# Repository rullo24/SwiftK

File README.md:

# SwiftK
SwiftK is an open-source project for creating a customizable macro keypad that integrates seamlessly with your workflow. Designed for developers, gamers, and productivity enthusiasts, SwiftK provides a streamlined way to enhance your interaction with your computer through user-defined macros.

## About SwiftK
SwiftK was created to make repetitive tasks more efficient by providing a versatile macro keypad solution. With customizable keys, users can map complex command sequences or simple shortcuts, tailored to their needs. SwiftK aims to make interactions more productive and enjoyable for users in programming, gaming, content creation, and more.

This GitHub repo holds the KiCAD files required for the creation of this electronic board.

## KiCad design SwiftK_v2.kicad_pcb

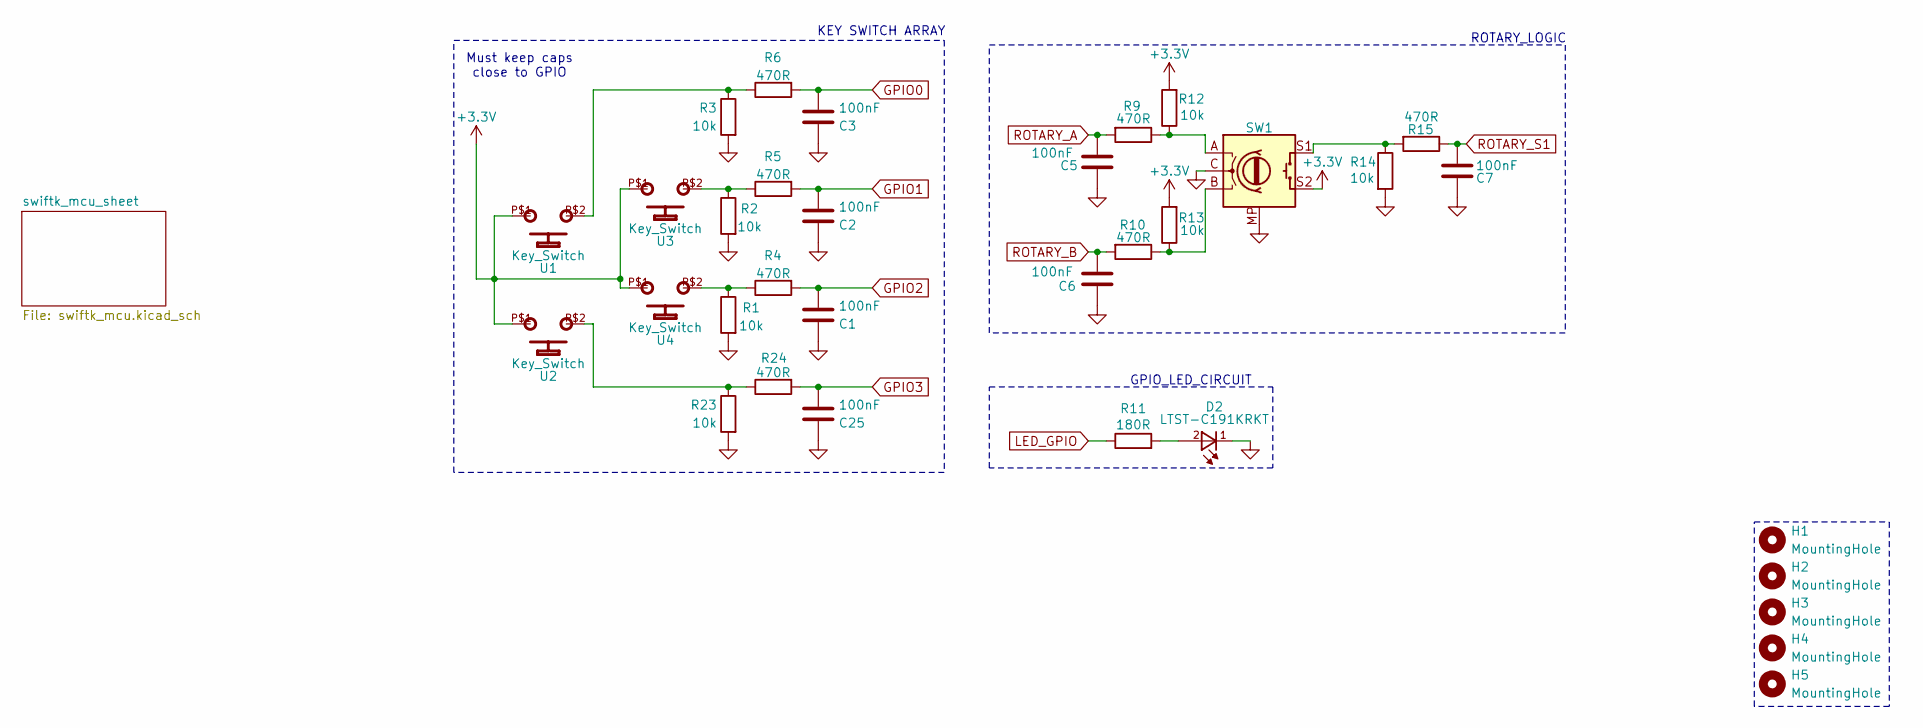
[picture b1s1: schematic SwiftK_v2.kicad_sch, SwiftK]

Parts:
C1, C2, C3, C5, C6, C7, C25: 100nF; C_0201_0603Metric; JLCPCB Part# C76928
D2: LTST-C191KRKT; liteon_LTST-C191KRKT; JLCPCB Part# C125099
H1, H2, H3, H4, H5: MountingHole; MountingHole_3.2mm_M3_DIN965_Pad
R1, R2, R3, R12, R13, R23: 10k; R_0201_0603Metric; JLCPCB Part# C100126
R4, R5, R6, R9, R10, R15, R24: 470R; R_0603_1608Metric; JLCPCB Part# C374403
R11: 180R; R_0603_1608Metric; JLCPCB Part# C25210
R14: 10k; R_0603_1608Metric; JLCPCB Part# C15401
SW1: RotaryEncoder_Switch_MP; RotaryEncoder_Alps_EC11E-Switch_Vertical_H20mm
U1, U2, U3, U4: Key_Switch; CHERRY_MX1A-11NN_SWITCH

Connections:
+3.3V: R12.2, R13.2, SW1.S2, U1.P$1, U2.P$1, U3.P$1, U4.P$1; also elsewhere on the board
GND: C1.1, C2.1, C3.1, C5.2, C6.2, C7.2, C25.1, D2.1, R1.2, R2.2, R3.2, R14.2, R23.2, SW1.C, SW1.MP; also elsewhere on the board
GPIO0: C3.2, R6.2; also elsewhere on the board
GPIO1: C2.2, R5.2; also elsewhere on the board
GPIO2: C1.2, R4.2; also elsewhere on the board
GPIO3: C25.2, R24.2; also elsewhere on the board
LED_GPIO: R11.1; also elsewhere on the board
unnamed: D2.2, R11.2
unnamed: R1.1, R4.1, U4.P$2
unnamed: R2.1, R5.1, U3.P$2
unnamed: R3.1, R6.1, U1.P$2
unnamed: R10.1, R13.1, SW1.B
unnamed: R9.1, R12.1, SW1.A
unnamed: R14.1, R15.2, SW1.S1
unnamed: R23.1, R24.1, U2.P$2
ROTARY_A: C5.1, R9.2; also elsewhere on the board
ROTARY_B: C6.1, R10.2; also elsewhere on the board
ROTARY_S1: C7.1, R15.1; also elsewhere on the board

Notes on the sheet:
Must keep caps close to GPIO
GPIO_LED_CIRCUIT
ROTARY_LOGIC
KEY SWITCH ARRAY

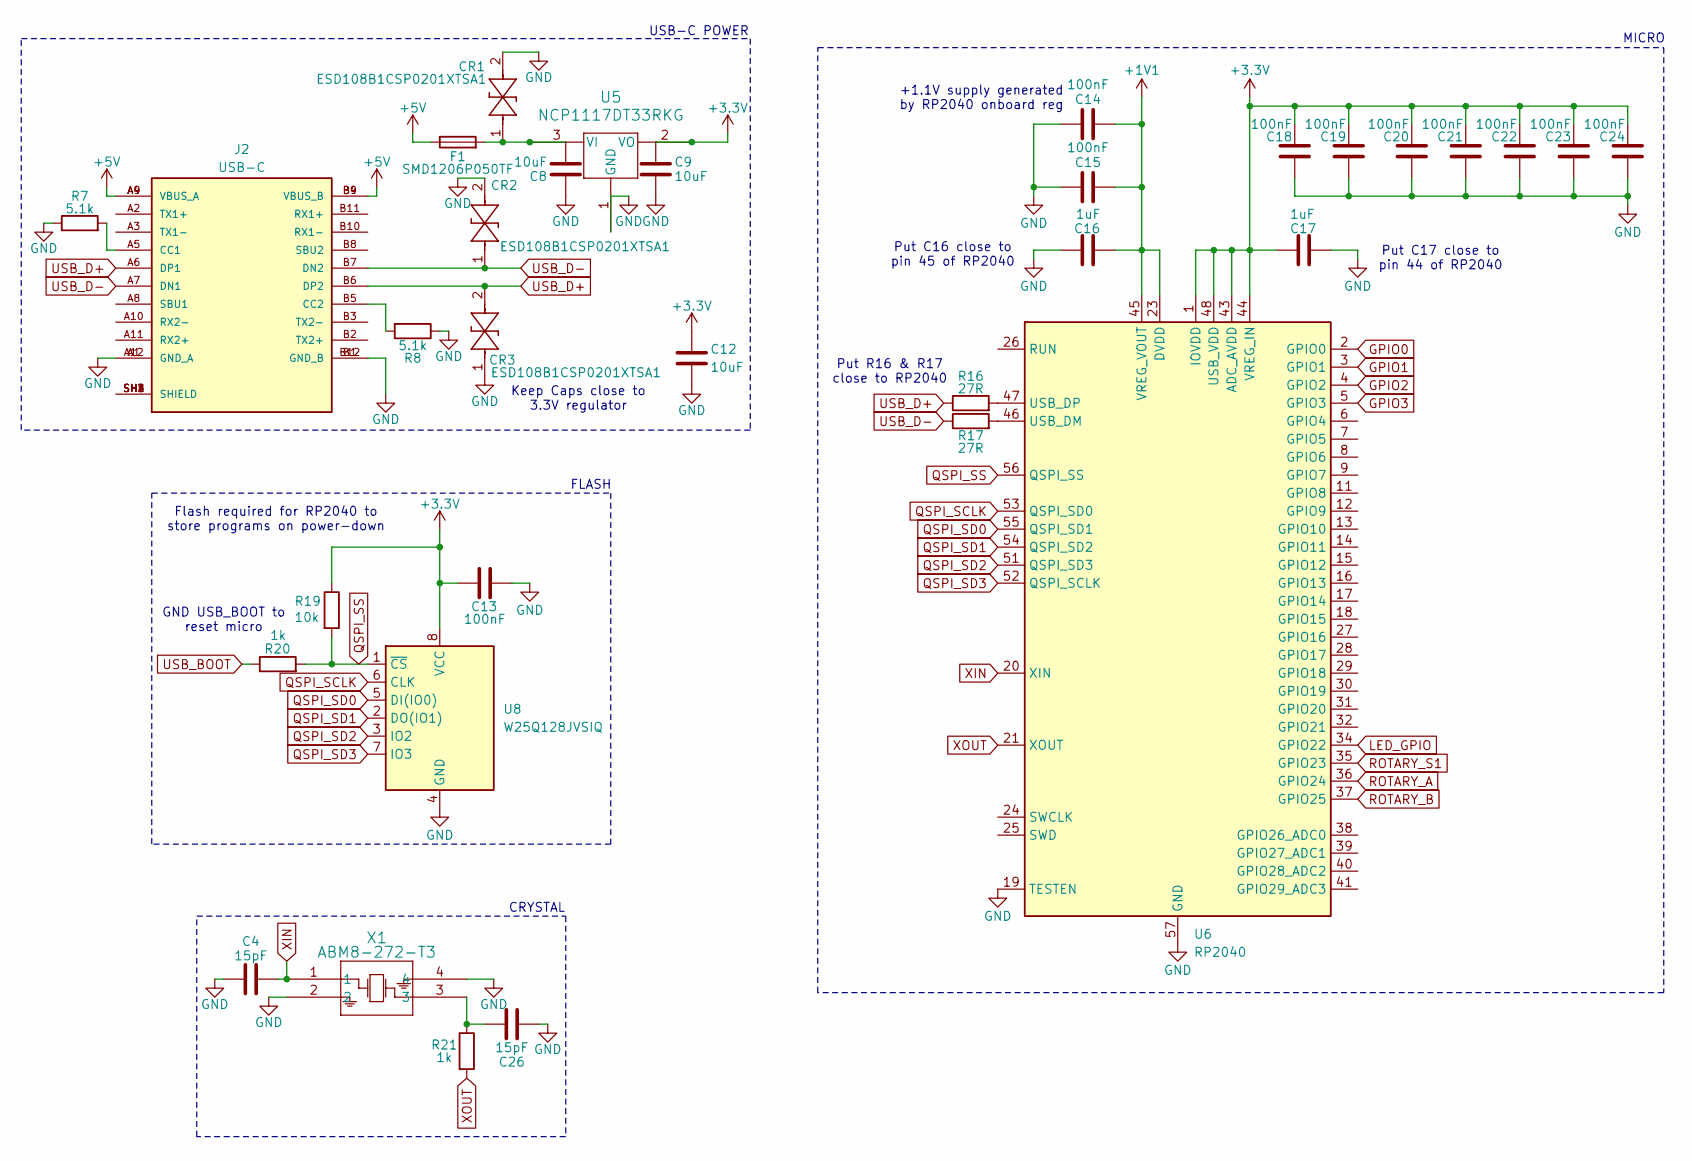
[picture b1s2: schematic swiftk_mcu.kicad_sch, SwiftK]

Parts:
C4, C26: 15pF; C_0603_1608Metric; JLCPCB Part# C1644
C8, C9, C12: 10uF; C_0603_1608Metric; JLCPCB Part# C18800
C13, C14, C15, C18, C19, C20, C21, C22, C23, C24: 100nF; C_0201_0603Metric; JLCPCB Part# C76928
C16, C17: 1uF; C_0201_0603Metric; JLCPCB Part# C76929
CR1, CR2, CR3: ESD108B1CSP0201XTSA1; Infineon_ESD108B1CSP0201XTSA1_L; JLCPCB Part# C672056
F1: SMD1206P050TF; Fuse_1206_3216Metric; JLCPCB Part# C20799
J2: USB-C; te_connectivity_2345986-1; JLCPCB Part# C5382687
R7, R8: 5.1k; R_0201_0603Metric; JLCPCB Part# C100142
R16, R17: 27R; R_1206_3216Metric; JLCPCB Part# C17946
R19: 10k; R_0603_1608Metric; JLCPCB Part# C15401
R20, R21: 1k; R_0603_1608Metric; JLCPCB Part# C51218
U5: NCP1117DT33RKG; onsemi_NCP1117DT33RKG_S; JLCPCB Part# C88234
U6: RP2040; QFN-56-1EP_7x7mm_P0.4mm_EP3.2x3.2mm; JLCPCB Part# C2040
U8: W25Q128JVSIQ; Winbond_Elec_W25Q128JVSIQ; JLCPCB Part# C97521
X1: ABM8-272-T3; Abracon_LLC_ABM8-272-T3; JLCPCB Part# C20625731

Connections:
+1V1: C14.2, C15.2, C16.1, U6.23 (DVDD), U6.45 (VREG_VOUT), U6.50 (DVDD)
+3.3V: C9.1, C12.1, C13.2, C17.2, C18.2, C19.2, C20.2, C21.2, C22.2, C23.2, C24.2, R19.1, U5.2 (VO), U6.1 (IOVDD), U6.10 (IOVDD), U6.22 (IOVDD), U6.33 (IOVDD), U6.42 (IOVDD), U6.43 (ADC_AVDD), U6.44 (VREG_IN), U6.48 (USB_VDD), U6.49 (IOVDD), U8.8 (VCC); also elsewhere on the board
+5V: F1.1, J2.A4 (VBUS_A), J2.A9 (VBUS_A), J2.B4 (VBUS_B), J2.B9 (VBUS_B)
GND: C4.1, C8.1, C9.2, C12.2, C13.1, C14.1, C15.1, C16.2, C17.1, C18.1, C19.1, C20.1, C21.1, C22.1, C23.1, C24.1, C26.1, CR1.2, CR2.2, CR3.1, J2.A1 (GND_A), J2.A12 (GND_A), J2.B1 (GND_B), J2.B12 (GND_B), R7.1, R8.1, U5.1 (GND), U6.19 (TESTEN), U6.57 (GND), U8.4 (GND), X1.2, X1.4; also elsewhere on the board
GPIO0: U6.2 (GPIO0); also elsewhere on the board
GPIO1: U6.3 (GPIO1); also elsewhere on the board
GPIO2: U6.4 (GPIO2); also elsewhere on the board
GPIO3: U6.5 (GPIO3); also elsewhere on the board
LED_GPIO: U6.34 (GPIO22); also elsewhere on the board
unnamed: C26.2, R21.1, X1.3
unnamed: J2.A5 (CC1), R7.2
unnamed: J2.B5 (CC2), R8.2
unnamed: J2.SH1 (SHIELD), J2.SH2 (SHIELD), J2.SH3 (SHIELD), J2.SH4 (SHIELD)
unnamed: C8.2, CR1.1, F1.2, U5.3 (VI)
unnamed: R17.2, U6.46 (USB_DM)
unnamed: R16.2, U6.47 (USB_DP)
QSPI_SCLK: U6.53 (QSPI_SD0), U8.6 (CLK)
QSPI_SD0: U6.55 (QSPI_SD1), U8.5 (DI(IO0))
QSPI_SD1: U6.54 (QSPI_SD2), U8.2 (DO(IO1))
QSPI_SD2: U6.51 (QSPI_SD3), U8.3 (IO2)
QSPI_SD3: U6.52 (QSPI_SCLK), U8.7 (IO3)
QSPI_SS: R19.2, R20.2, U6.56 (QSPI_SS), U8.1 (~CS)
ROTARY_A: U6.36 (GPIO24); also elsewhere on the board
ROTARY_B: U6.37 (GPIO25); also elsewhere on the board
ROTARY_S1: U6.35 (GPIO23); also elsewhere on the board
USB_BOOT: R20.1
USB_D+: CR3.2, J2.A6 (DP1), J2.B6 (DP2), R16.1
USB_D-: CR2.1, J2.A7 (DN1), J2.B7 (DN2), R17.1
XIN: C4.2, U6.20 (XIN), X1.1
XOUT: R21.2, U6.21 (XOUT)

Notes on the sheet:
Keep Caps close to 3.3V regulator
USB-C POWER
Put C16 close to pin 45 of RP2040
Flash required for RP2040 to store programs on power-down
FLASH
CRYSTAL
GND USB_BOOT to reset micro
MICRO
Put C17 close to pin 44 of RP2040
Put R16 & R17 close to RP2040
+1.1V supply generated by RP2040 onboard reg

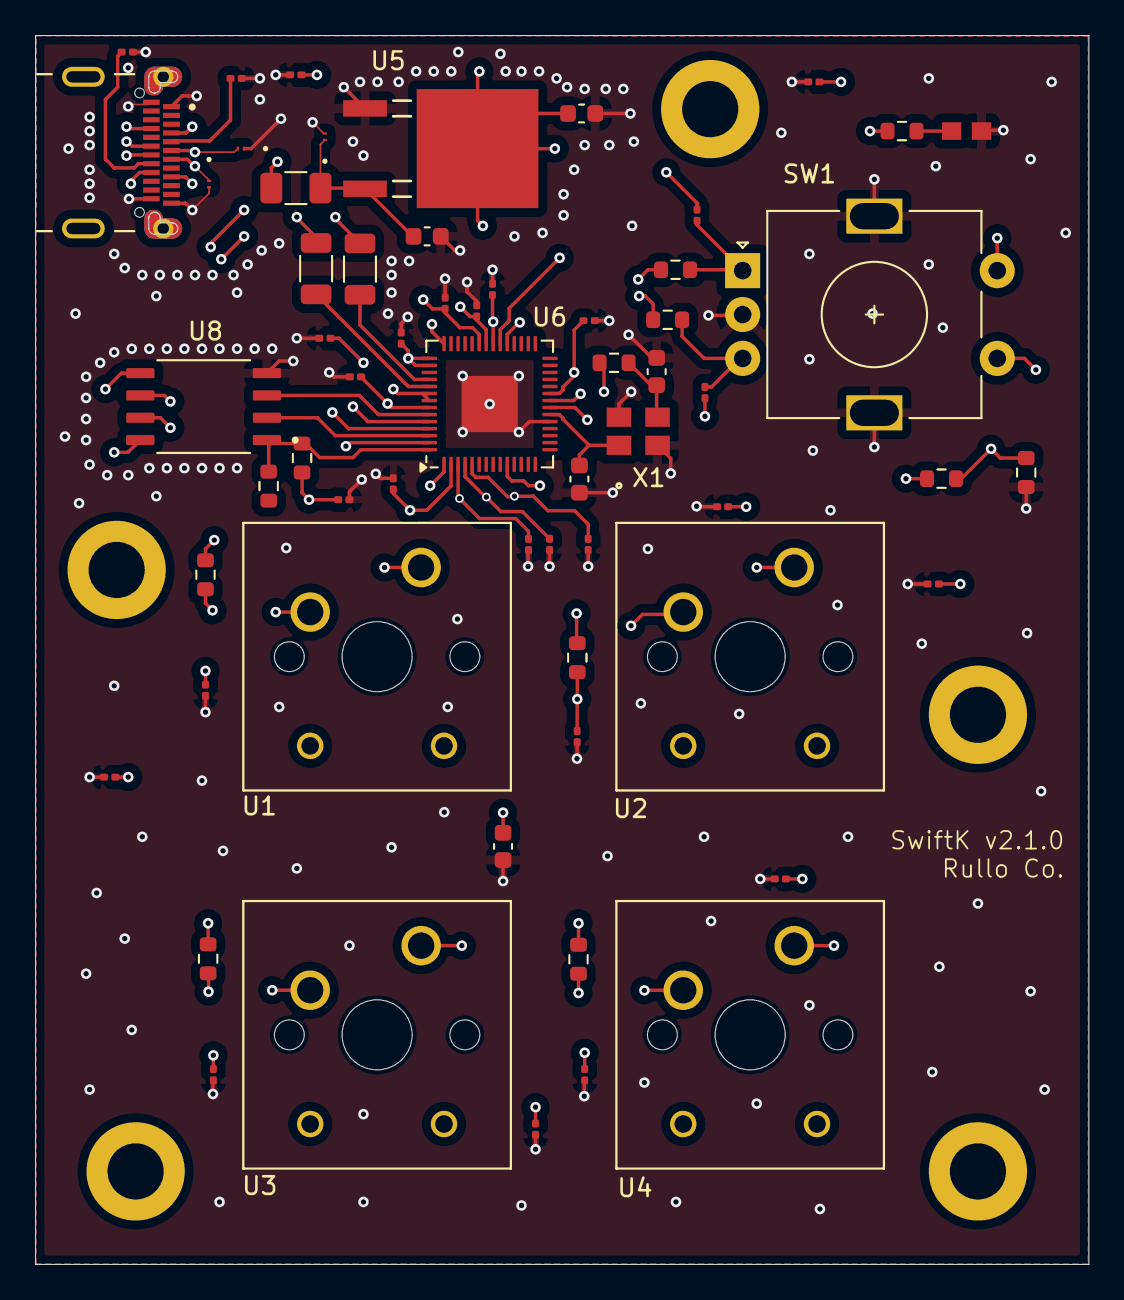
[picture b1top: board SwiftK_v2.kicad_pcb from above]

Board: 4 copper layers, 60.0 x 70.0 mm, 66 parts (0 on the bottom side), 37 nets.

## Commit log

2024-11-11 V2.1.0 SwiftK Complete
2024-11-11 Added README
